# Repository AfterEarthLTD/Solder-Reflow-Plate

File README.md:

# **Working with an ATmega4809**

https://github.com/gotnull/Solder-Reflow-Plate/blob/main/Board%20Versions/70mm%20by%2050mm%20Ver3.0%20ATmega4809/Software/SW1.0_HW3.0_70by50mm.ino

**To Prepare**

1. Include MiniCoreX in additional boards via the Arduino IDE Boards Manager: https://mcudude.github.io/MegaCoreX/package_MCUdude_MegaCoreX_index.json
3. Install Bounce2, Adafruit_GFX and Adafruit_SSD1306 libraries (Tools->Manage Libraries)

**To Program**

1. Select the following settings under (Tools)

- Board->MegaCoreX->ATmega4809
- Clock->Internal 16MHz
- BOD->BOD 2.6V
- EEPROM->EEPROM retained
- Pinout->48 pin standard
- Reset pin->Reset
- Compiler LTO->LTO Disabled
- Bootloader->No bootloader

**Compile to ATmega4809**

I followed this guide here: https://swharden.com/blog/2022-12-09-avr-programming/

**Specifically this setup:**

Connect the programmer as shown with the RX pin directly to the UPDI pin of the microcontroller and the resistor between the RX and TX pins. IMPORTANT: The Reflow Plate must be powered externally via 12V with a minimum of 5A during this process.

I used a 10KΩ 0.5W resistor instead. This is even closer to the recommended value. 10KΩ is a common pull-up resistor value used in many electronics applications. It should work well for the UPDI interface.

Ensure a [modern version of Python](https://www.python.org/) is installed on your system

`pip install pymcuprog`

Use the device manager to identify the name of the COM port representing your programmer. In my case it was `/dev/tty/usb.serial-AH00XXXX` on MacOS.

I then interacted with the microcontroller by running `pymcuprog` from a terminal. This command returns the Device ID (1E9651 for my ATmega4809) indicating the UPDI connection is working successfully.

`pymcuprog ping -d atmega4809 -t uart -u /dev/tty.usbserial-AH00XXXX`

> Connecting to SerialUPDI
> Pinging device...
> Ping response: 1E9651
> Done.

I used Arduino IDE to compile my C code and generate the hex file (turn on verbose output during compilation to know the location of your `.ino.hex` file). Now you can use `pymcuprog` to load the hex file onto the chip. It’s slower to program and inconvenient to drop to a terminal whenever you want to program the chip, but it works.

`pymcuprog write -f SW1.0_HW3.0_70by50mm.ino.hex -d atmega4809 -t uart -u /dev/tty.usbserial-AH00XXXX --erase`

> Connecting to SerialUPDI
> Pinging device...
> Ping response: 1E9651
> Erasing device before writing from hex file...
> Writing from hex file...
> Writing flash...
> Done.

# **Solder Reflow Plate**

###### By AfterEarth Ltd

## As Seen On GreatScott! 

This project has recently featured on a DIY or BUY GreatScott! video.

Check it out here - [The Best way to reflow solder? Hot Plate to the rescue! DIY or Buy](https://www.youtube.com/watch?v=QarizoUnRfk)

## UPDATE!!!

Join the [DISCORD!](https://discord.gg/YzhG6FcCRA)

Checkout the new Ver 3.0 design. Very similar to Ver 2.4 but now comes with ATmega4809 as its availability is much better than the 328p at the moment. Code is still in development but the board designs are available in the Board Versions Folder.

## Versions

- 70mm x 50mm (Ver 2.4)
  - 12VDC (5A Minimum)
  - 5.5mm x 2.5mm Barrel Jack
  - 0.91" OLED Display
  - ATmega328p Microprocessor

- 70mm x 50mm (Ver 3.0) **NEW**
  - 12VDC (5A Minimum)
  - 5.5mm x 2.5mm Barrel Jack
  - 0.91" OLED Display
  - ATmega4809 Microprocessor

## About the Project

Like any good nerd does I've been expanding my hobby horizons.
I've gone from breadboard, to perf board, through-hole, to SMD, ever increasing circuit complexity and improving my knowledge.
But I've become frustrated with the difficulty of SMD soldering.
Regular soldering jogs small components and needs lots of flux.
Hot air damages plastics.
Hot plates are expensive and can be big wastes of space.

*"But you're a nerd"* I hear you cry, *"why don't you DIY a solution?"*.

[Electronoobs](https://www.youtube.com/channel/UCjiVhIvGmRZixSzupD0sS9Q) shows a great DIY solution using an old clothes iron hot plate.
You can watch his video [here.](https://www.youtube.com/watch?v=C7blZigaaaA)
Have a go!

While I love this solution, I wanted to develop something smaller and more permanent.
Hence the Solder Reflow Plate was born, a PCB-based, MOSFET controlled heater, perfect for easily reflowing SMD components giving surprisingly professional results. Furthermore, these results are achieved without breaking the bank or taking up an enormous amount of desk space.

And so, this nerd bestows upon the world his project, fully open-source and hackable.
Here's hoping that it may be used to develop skills, build custom circuit boards, and make quality designs possible to all!

## Purchase

- Register your email address at [www.solderreflowplate.co.uk](https://www.solderreflowplate.co.uk) to know when it is available to buy!
- There is a worldwide shortage of ATmega328p Microcontrollers. I'm currently working on a small redesign for a more readily available chip.
- Purchase will be available soon!

## License

All parts of this project are covered by a [MIT license](LICENSE).
That means it is entirely open-source, so you get access to everything! (just without warranty or liability)
Feel free to download, customise, hack, and commercialise to your nerdy heart's content.

Want the **easy** life?!
**Purchase** the default design above!
Its fully functional, cheaper than customising, and helps to feed the creator's caffeine addiction 🙃

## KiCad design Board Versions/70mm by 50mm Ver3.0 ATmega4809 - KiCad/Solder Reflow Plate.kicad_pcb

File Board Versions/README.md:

# **Designing Your Own Hotplate**

If you're the kind of person interested in building a project like this, you may also be the kind of person who might want to improve upon it or adjust it for a different operating environment. For example, you may want to operate from a higher voltage supply, design a larger sized hotplate or other similar options. What do we know from this design that could help inform such modifications?

My experience with hotplate design is based on designing separate hotplates (ie. without integrated electronics onboard) that fall within the size limitations of the cheap Chinese PCB manufacturers (ie. 100x100mm maximum size). The heated area of my hotplates are roughly 86mm square due to allowances for mounting the hotplate. Secondly, I am designing for reflowing traditional Tin-Lead (SnPb) solder alloys, which melt at approximately 180 celsius. If you are only intersted in reflowing lower temperature solder alloys like Tin-Bismith (SnBi) alloys, the power requirements can be lowered slightly. The common commercial lead-free alloys (ie. SAC305, SAC405, etc) are probably unsuitable for reflowing on a PCB based hotplate, so this discussion will not consider them.

## Decide on Target Heating Power ##

Calibration data from my hotplates suggest that a hotplate of that shape and size has a thermal resistance to ambient air of about 2.4 K/W. For reflowing SnPb, you want to aim for a peak temperature of at least 205 celsius. This is lower than most commercial reflow profiles, but from my experience this is more than hot enough to get reliable and repeatable results. For SnBi, typical reflow profiles aim for around 180 celsius peak temperatures. Assuming that we have an ambient air temperature of about 20 celsius, then we're looking to support a temperature delta of about 160 kelvin for SnBi or about 185 kelvin for SnPb. For SnPb, the calculations end up being:

$$\frac{185 K}{2.4 K/W} = ~77 W$$

That is how much power you need to simply maintain that temperature against ambient air at 20 celsius. To get there in a reasonable amount of time, you will need more. My rule of thumb is to add 20-50% more power. Higher power will allow you to achieve higher temperature gradients and improve your ability to closely follow a reflow profile. 20% additional power should be good enough to achieve reliable and repeatable results but may struggle with some of the steeper temperature gradients during preheat in some reflow profiles. 50% should give you more than enough power to follow most reflow profiles pretty closely. So for a hotplate my size to reflow SnPb solder we're looking at somewhere around 90-115W as a good range of power to aim for in our heating element. If you do the calculations for SnBi, you get slightly lower power range of about 80-100W. Note that you can reflow either of these alloys with less power, but you will need to trade off either hotplate size or heating speed or both in order to do this.

One last comment on heating power requirements... If you're designing a different sized hotplate, you will need to scale these numbers somehow. While I doubt this will scale linearly, in the absence of a better theoretical model, I would suggest starting with linearly scaling the power requirement by area. My heating element area is close to 75 square centimetres, so the holding power required is roughly 1W per square centimetre. This makes the target power range to be roughly 1.2 - 1.5 W per square centimetre of heating element. Given how heat transfer works, I expect smaller hotplates will lose heat to the environment more quickly than larger hotplates, so these numbers may estimate low for smaller sizes and might estimate high for larger hotplates. That's just a guess on my part. For smaller hotplates, I'd err closer to the 1.5 W per square centimetre to be safe. For larger hotplates, if you're power constrained, you may be able to work closer to 1.2 W per square centimetre or possibly lower and still get decent results.

## Drive Voltage ##

Let's assume you're designing to run from something like a laptop power brick or USB-PD supply. Laptop power bricks commonly output 19V and are often rated at 90W or more. USB-PD can support voltages up to 20V at currents up to 5A, so 100W. We'll work with the laptop power brick specs, as the lower specs will be more limiting for our hotplate perforance, but I expect these results will still work reasonably well for USB-PD and give us a hotplate that can be supported by a wide range of available hardware that's already out there in the world.

Before we get carried away, we also need to consider the impacts of PWM and the maximum practical duty cycle we can use. Because of a variety of factors, such as non-zero turn-on and turn-off times, it's not really practical to operate all the way up to 100% duty cycle. Realistically, the highest practical duty cycle value is likely around 95% or less. The effect of this is that our maximum operating voltage for the heating element is reduced to 95% of our power supply voltage. If you want to limit duty cycle to some lower value than 95%, then use that percentage as well.

Additionally, our power conversion electronics will not be 100% efficient. For the purpose of these calculations, we're going to assume around 95% efficiency ($\eta$). This may be optimistic, so you may want to choose a lower value depending on your own experience.

$$ V_{operating} = V_{supply} \times D_{max} \times \eta $$

$$ V_{operating} = 19 \times 0.95 \times 0.95 = 17.15 V $$

From ohm's law, we have that the power dissipated in the heating element is:

$$ P_{heating element} = \frac{V_{operating}^2}{R_{heating element}} $$

Rearranging to calculate required resistance from voltage and power:

$$ R_{heating element} = \frac{V_{operating}^2}{P_{heating element}} $$

$$ R_{heating element} = \frac{17.15 \times 17.15}{90} = 3.27 \Omega $$

## Resistance Versus Temperature ##

We need to allow for the fact that our heating element's resistance will increase as it gets hotter. In fact, this is one good option you can use to determine the temperature of the hotplate if your control scheme has access to accurate real-time voltage and current information from the hotplate. It's impractical to try to be overly precise as there can be substantial variation between boards in a batch as well as process variation between batches and between manufacturers. Because of this, it's probably not worth more than a rough approximation here. At reflow temperatures, your heating element's resistance will be roughly 70% higher than it will be at ambient temperatures. I typically take the resistance value calculated above as the resistance of the heating element at peak temperature (ie. when "hot"), so to determine the target resistance for my heating element at ambient temperatures, I take the number from above and divide it by 1.7.

$$ \frac{3.27 \Omega}{1.7} = 1.92 \Omega $$

That's the value I design for in my heating element.

## PCB Design To Resistance ##

Some PCB design software may provide tools for estimating the resistance of PCB traces. In the absence of that, the following approach may be close enough, although from my results, I suspect that what happens around corners or at changes in trace width may be more complex than this model allows, so if your design includes very large numbers of corners or variations in width, the real world results may be different from what you get from this calculation.

To calculate the resistance of a linear trace of constant width, you would use the formula:

$$ R = \frac{\rho \times length}{width \times thickness} $$

where $\rho$ is the resistivity of the material in $\Omega m$ and length, width and thickness are all distances measured in *metres*. For 1 oz copper, the theoretical thickness of the copper foil on a PCB would be about $35 \times 10^{-6} m$ thick (ie. 0.0000035m thick). For annealed copper, $\rho$ is about $1.72 \times 10^{-8} \Omega m$. So for a copper trace 1.5mm wide, 70mm long in 1 oz copper, we would have

$$ R = \frac{1.72 \times 10^{-8} \times 0.07}{0.0015 \times 0.000035} = 0.02293 \Omega $$

or about 23 $m\Omega$. From working with JLCPCB for some of our earlier revisions, the actual resistances seemed to suggest that the copper thickness may be closer to 29 microns (ie. 0.000029m) than the 35 microns we expect. Although I now recommend PCBWay as a better option for manufacturing hotplates, I have less experience with them so far. I think 29 microns may also be a reasonable approximation of copper thickness there, but I have had some surprising results with some of my later, more complex layouts, so maybe my expectations are wrong or some process has changed at PCBWay in recent months. Your mileage may vary. Based on this, we can proceed as follows:

1. Break your heating element up into a series of linear traces with constant width.
1. For each linear trace, measure the length of the trace along the centre of the trace. The ends of each trace should touch the ends of neighbouring traces, so at a corner the end would be in the mid-point of the corner for both traces entering or leaving that corner.
1. Sum the lengths of all the traces with the same width.
1. Calculate the total resistance for each trace width you have using the formula as shown above.
1. Sum all of the resistances calculated for each different trace width.

That last number is the estimated resistance of the entire heating element. It can take some trial and error to dial in the resistance just where you want it, so be patient. Alternatively, use someone else's well tested design if it's close enough to your design requirements.

Hopefully this gives enough of a background that someone interested in the challenge of designing their own hotplate can get a start without having to reinvent everything. Good Luck!

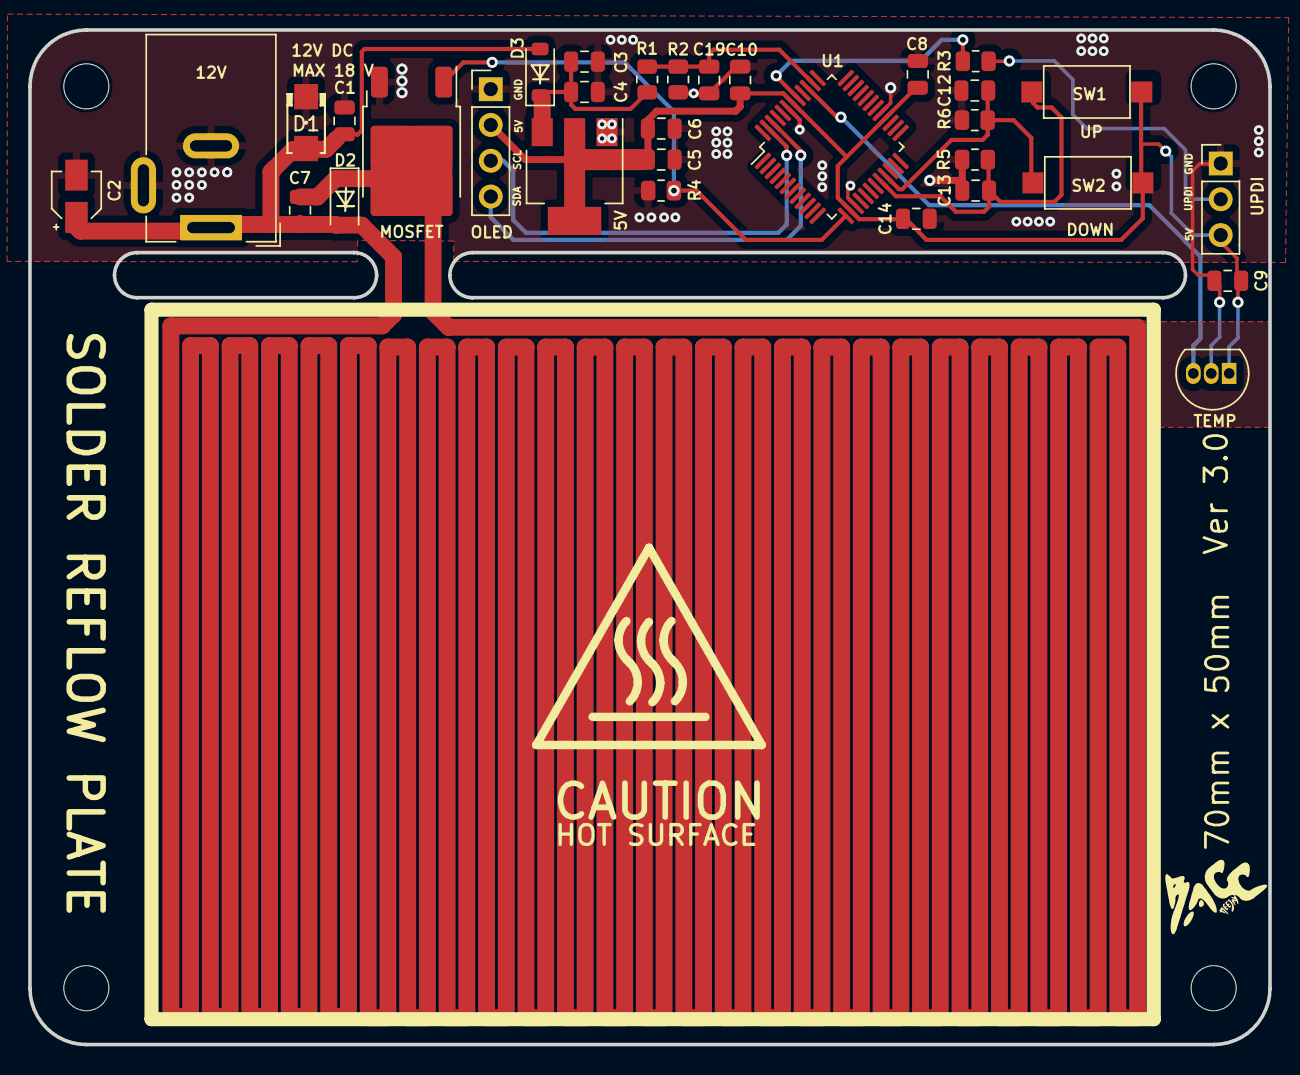
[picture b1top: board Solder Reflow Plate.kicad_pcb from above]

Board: 2 copper layers, 88.0 x 72.0 mm, 36 parts (0 on the bottom side), 13 nets.

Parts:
5V: AMS1117-5.0; SOT-223-3_TabPin2
12V: DC-005-5A-2.5; BarrelJack_Wuerth_6941xx301002
C1, C4, C6, C9, C19: 100nF; C_0805_2012Metric
C2: 100uF; CP_Elec_3x5.3
C3: 22uF; C_0805_2012Metric
C5: 22nF; C_0805_2012Metric
C7: 1nF; C_0805_2012Metric
C8, C10, C12, C13, C14: 10nF; C_0805_2012Metric
D1: SMAJ58A; D_DO-214AC_SMA
D2: MM1Z24; D_SOD-123
D3: DSR1M_C908221; D_SOD-123
H1, H2, H3, H4: MountingHole_Pad; MountingHole_3.2mm_M3
MOSFET: UMW30N06; TO-252-2
OLED: PinHeader_1x04_P2.54mm_Vertical
R1: 3K; R_0805_2012Metric
R2: 1K; R_0805_2012Metric
R3, R5, R6: 4.7K; R_0805_2012Metric
R4: 10K; R_0805_2012Metric
SW1: UPSW; SW_SPST_CK_RS282G05A3
SW2: DNSW; SW_SPST_CK_RS282G05A3
TEMP: LMT85LP; TO-92L_Inline
U1: ATmega4809-A; TQFP-48_7x7mm_P0.5mm
UPDI: UPDI Header; PinHeader_1x03_P2.54mm_Vertical

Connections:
+5V: 5V.2 (VO), C5.1, C6.1, C8.1, C9.1, C10.1, C14.1, OLED.2 (VCC), SW1.1, SW2.1, TEMP.1 (V_{DD}), U1.14 (VCC), U1.28 (AVCC), U1.42 (VCC), UPDI.3
DNSW: C12.1, R6.2, SW2.2, U1.21 (PD1)
GND: 5V.1 (GND), 12V.2, 12V.3, C1.2, C2.2, C3.2, C4.2, C5.2, C6.2, C8.2, C9.2, C10.2, C12.2, C13.2, C14.2, C19.2, D1.1 (A1), MOSFET.3 (S), OLED.1 (GND), R2.1, R4.1, R5.1, R6.1, TEMP.2 (GND), U1.15 (GND), U1.29 (GND), U1.43 (GND), UPDI.1
Gate: MOSFET.1 (G), R4.2, U1.13 (PC3)
HEATING_ELEMENT: 12V.1, C1.1, C2.1, C7.1, C7.2, D1.2 (A2), D2.1 (K), D2.2 (A), D3.2 (A), MOSFET.2 (D)
unnamed: R3.1, UPDI.2
SCLOLED: OLED.3 (SCL), U1.47 (PA3)
SDAOLED: OLED.4 (SDA), U1.46 (PA2)
TempData: TEMP.3 (OUT), U1.39 (PF5)
UPDI: R3.2, U1.41 (UPDI)
UPSW: C13.1, R5.2, SW1.2, U1.20 (PD0)
VIND: 5V.3 (VI), C3.1, C4.1, D3.1 (K), R1.1
VccDiv: C19.1, R1.2, R2.2, U1.38 (PF4)

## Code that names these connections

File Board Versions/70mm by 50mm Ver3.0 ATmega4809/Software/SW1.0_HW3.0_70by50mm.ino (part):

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Adafruit_SSD1306 display(SCREEN_WIDTH, SCREEN_HEIGHT, &Wire, -1); //Create Display

//Pin Definitions
#define mosfet PIN_PC3
#define upsw PIN_PD0
#define dnsw PIN_PD1
#define temp PIN_PF5 // MegaCoreX board required
#define vcc PIN_PF3 // MegaCoreX board required

Bounce2::Button upButton;
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
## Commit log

2021-11-05 Initial Write-up
2021-11-05 Linked license doc
2022-01-13 Document Updates
    Created 2x How-To documents
    Updated Readme
2022-01-23 Uploaded Software
    - Uploaded SW1.0 HW2.4
    - Wrote SW Revisions doc
    - Removed references to AfterEarthLTD
2022-02-03 Various Documentation
    Wrote how to build stock board
    Updated links in lots of others
    Wrote Software revisions doc
2022-02-03 Updated
    Fine Tuning Heat Process Code
    Small doc updates
2022-02-03 Board Files
    Added all major board files.
    Updated Sketch heating, removed thickness and limited to 180C.
2022-02-03 Update issue templates
2022-02-16 Added Photos of Dev Ver2.3
2022-02-16 Added Photos of Ver2.3
2022-02-16 Updated Readme to link to GreatScott! Video
2022-02-16 Updated Readme to prevent markdown errors
2022-02-27 Fixed broken link in README
2022-02-27 Update readme with working external link
2022-02-28 Added EasyEDA Schematic File
2022-03-02 Update SW1.0_HW2.4_70by50mm.ino
    make into a state machine
2022-03-02 Schematic and PCB
2022-03-02 3d view
2022-03-03 changed mosfet to Logic Level Mosfet
    Added a second Mosfet/ changed to Logic Level Mosfet
2022-03-04 Linked Discord in README
2022-03-04 Added docs from Ver3.0 Board based on 4809.
2022-03-13 'Debounce' section of code now a function. Button reader function to abstract and debounce 'digitalRead()' Minor variable tweaks and checks.
2022-03-14 Updated Discord Link & Fixed Pick and Place files.
    -Issue with OLED 0.91" tricking conversion into .csv
2022-03-26 Smaller table
2022-03-26 Changed to 0805/0603 from 0402
    Changed Capacitors from 0402 to 0805/0603
    Changed Buttons to internal PullUP
2022-03-31 Fix idle screen display
2022-03-31 Fix for no heating
2022-03-31 New error state for temperature related problems
2022-04-03 Reversed
2022-04-03 Temperature not being drawn correctly
2022-04-23 Update BOM_SRP 70_50mm_Release_2022-03-04.csv
    Updated 3.0 BOM to allow
2022-04-23 Update PickAndPlace_SRP 70_50mm_Release_2022-03-04.csv
    V3.0 Pick and Place CSV Beautify
2022-04-23 Update BOM_SRP 70_50mm_Release_2022-02-03.csv
    V2.4 BOM Beautify
2022-04-23 Update PickAndPlace_SRP 70_50mm_Release_2022-02-03.csv
    V2.4 Pick and Place CSV Beautify
2022-05-19 Moved .ino file to subdirectory with same name to make Arduino IDE happy.
2022-05-19 Updated build information in the header comments. Updated hw version to 3.0
2022-05-19 Added additional temperature settings for the brave.
2022-05-19 Reversed up and down buttons so the upper button does up and the lower button does down.
2022-05-19 Try to avoid spurious cancellations by requiring both buttons to be pressed for cancellation.
2022-05-19 Updated on-screen text to match current system behaviour.
2022-05-19 Minor updates on OLED screen sources and initial SMD soldering options.
2022-05-19 Minor changes to V3.0 build markdown file.
2022-05-19 Updated the programming instructions markdown file for V3.0 hardware.
2022-05-19 Added return 1 to end of heat functon so that the calling function can know when the cycle completed successfully. fix #1
2022-05-29 docs: formatting
    Improve github markdown formatting.
2022-07-07 Added warnings regarding lack of safety features.
2022-11-07 Version 3 Software
2022-12-16 Added Digikey/Mouser BOM file.
2023-02-07 Added design considerations for improvements to README.md.
2023-02-07 Added comment regarding resistance at reflow versus ambient temperatures in design considerations.
2023-02-15 Fixed typos in programming instructions.
2023-02-16 Updated programming instructions with details on options to power the MCU during programming.
2023-02-16 Removed 5V pin unconnected comment, as inconsistent with MCU power options.
2023-02-18 Updated README to note the hot inpput capacitor issues on v2.4 and modify the firmware to avoid overheating input caps.
2023-02-20 Create SW1.0_HW3.0_70by50mm.ino
    The 2.4 version built using ATMEGA328P was modified to work with ATMEGA4809.
2023-02-26 Updated MOSFET to higher spec part with lower Rds(on) to avoid MOSFET getting hot.
2023-02-26 Added FAST_PWM define to turn FAST_PWM on and off, including altered messaging to make it clear when FAST_PWM is enabled.
2023-02-26 Updated comments about power filtering for the heating element PWM to address issues like input capacitor overheating and excessive loading back on the power supply.
2023-02-26 Added comments about the FAST_PWM macro for controlling PWM frequency.
2023-03-01 Solder Reflow Plate 70*50 mm Designed with KiCad
    This version is made in KiCad, there is no big changes, the only few things that change are the R and C package that are all 0805. Also the UP/DOWN SWITCH are changed using smd ones
2023-03-01 Delete Board Versions/70mm by 50mm Ver3.0 ATmega4809 - KiCad directory
    Deleting the diectroy to upload a clean one
2023-03-01 New directory w/schematics and PCB layout - KiCAD
    Based on Solder Reflow Plate 70.50 ver 3.0, but made in KiCAD.
    Changes:
    - Resistor & Capacitor Footprints changed to 0805
    - D1 changed to SMAJ58A w/package DO-214
    - SMD 2-Pin Switches
    - Added Plated mounting hole
2023-03-13 Added README.md file in Board Versions directory to discuss hotplate design considerations.
2023-03-13 Some grammar improvements and mathematical corrections. "Hot" resistance is closer to 70% higher than ambient resistance.
2023-03-13 Minor grammar corrections in hotplate design README.
2023-04-25 Updated calculations to allow for maximum duty cycle and power conversion efficiency impacts.
2023-04-25 First test with MathJax equation content in README.md.
2023-04-25 More equations updated to use MathJax.
2023-04-25 Updated final formulas and calculations to use MathJax content for hotplate design calculations.
2023-04-25 Fixed typo in MathJax equation. Updated more figures and formulas missed in the last edit.
2023-04-25 Fixed delimiters around inline MathJax content.
2023-04-25 Test for inline MathJax.
2023-04-25 Second attempt at fixing inline MathJax.
2023-04-25 Possible final MathJax edit for hotplate design calculations.
2023-04-25 Final MathJax fixes for some inline resistance and resistivity units in the hotplate design guidelines.
2023-04-27 Removed unimplemented features from Revisions.md. Updated file to more accurately reflect current functionality and include suggestions for firmware improvements.
2023-04-27 Renamed Revisions.md to README.md so it automatically renders on github.
2023-08-10 Create SW1.0_HW3.0_70by50mm.ino
    Updated for atmega4809
